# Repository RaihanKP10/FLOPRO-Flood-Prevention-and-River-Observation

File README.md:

# FLOPRO : Flood Prevention and River Observation

Proyek ini adalah Sistem Pemantauan Ketinggian Air Sungai yang menggunakan teknologi IoT untuk memberikan peringatan banjir secara real-time dengan mengukur ketinggian air sungai. Sistem ini dirancang untuk membantu manajemen bencana banjir dengan memberikan notifikasi kepada pemerintah daerah dan masyarakat tentang peningkatan ketinggian air, sehingga tindakan pencegahan dapat dilakukan sebelum banjir terjadi.

IoT dan Jaringan Sensor - [PROGRAM STUDI TEKNIK ELEKTRONIKA](https://elektronika.pens.ac.id/) - [POLITEKNIK ELEKTRONIKA NEGERI SURABAYA](https://www.pens.ac.id/)

`DOSEN PENGAMPU : Akhmad Hendriawan S.T.,M.T.`

`NIP. 197501272002121003`

## Daftar Isi
- [Fitur](https://github.com/RaihanKP10/FLOPRO-Flood-Prevention-and-River-Observation/blob/main/README.md#fitur)
- [Anggota Tim](https://github.com/RaihanKP10/FLOPRO-Flood-Prevention-and-River-Observation/blob/main/README.md#anggota-tim)
- [Demonstrasi Kalibrasi Sensor](https://github.com/RaihanKP10/FLOPRO-Flood-Prevention-and-River-Observation/blob/main/README.md#demonstrasi-kalibrasi-sensor)

## Fitur
- **Pemantauan Real-Time**: Mengukur ketinggian air sungai secara terus-menerus menggunakan sensor.
- **Transmisi Data**: Mengirimkan data ke server cloud melalui perangkat IoT.
- **Sistem Peringatan Banjir**: Memberikan peringatan ketika ketinggian air melebihi ambang batas.
- **Antarmuka Web dan Mobile**: Menampilkan data dan peringatan pada dasbor yang mudah digunakan.
- **Penyimpanan Data**: Menyimpan data untuk analisis dan prediksi.
- **Pengaturan Ambang Batas**: Menyesuaikan ambang batas sesuai tingkat risiko.

## Anggota Tim

| Foto                                                                                                          | NRP       | Nama                  | Jobdesk             | Akun                             |
|---------------------------------------------------------------------------------------------------------------|-----------|-----------------------|---------------------|----------------------------------|
|  | 2122600036 | Dafit Ody Endriantono | UI/UX Designer     | [Ody](https://github.com/DafitOdy-In) |
|  | 2122600037 | Thofail Syakirudin    | Hardware           | [Thofail](https://github.com/DzavanTS) |
|  | 2122600046 | Ahmad Miftahur Rif'at | Mechanical         | [Rif'at](https://github.com/AatForUX) |
|  | 2122600051 | Zanuar Dwi Novaliyanto | Mechanical         | [Zanuar](https://github.com/ZanuarDwiNovaliyanto) |
|  | 2122600056 | Moch Raihan Kemal P   | Software           | [Raihan](https://github.com/RaihanKP10) |
|  | 2122600060 | Asyraf Sulthan Zaky   | Project Manager    | [Asyraf](https://github.com/AsyrafSinclair) |

## Hardware Desain

Alat ini mengukur ketinggian air dengan sensor ultrasonik HCSR-04 dan mengirimkan data ke server untuk ditampilkan melalui aplikasi. Ketika ketinggian mendekati ambang batas, sistem memicu servo untuk membuka pintu air di bendungan. Karena alat berada di luar ruangan, data dikirim melalui modem WiFi, dan energi diperoleh dari panel surya mini yang disimpan dalam baterai.

---

---
## PPT FLOPRO

https://www.canva.com/design/DAGU0XxpfDs/OkEMPqyUYkoWt_qYXgOqGQ/edit?utm_content=DAGU0XxpfDs&utm_campaign=designshare&utm_medium=link2&utm_source=sharebutton

---

---

## Demonstrasi Kalibrasi Sensor
#### 1. Link Demonstrasi Kalibrasi Sensor HCSR04 :

https://github.com/user-attachments/assets/5eed2dfb-3297-49b0-9c64-bf10c1c43c4e
   
https://youtube.com/shorts/4SDvYGCIjRk?feature=share
   
Kalibrasi sensor HC-SR04 adalah proses penyesuaian sensor ultrasonik ini untuk meningkatkan akurasi dalam mengukur jarak. Sensor HC-SR04 bekerja dengan mengirimkan gelombang ultrasonik dari pemancar (transmitter) dan menghitung waktu yang dibutuhkan oleh gelombang tersebut untuk memantul kembali ke penerima (receiver) setelah mengenai suatu objek. Dengan menggunakan kecepatan suara sebagai acuan, sensor ini dapat menghitung jarak objek berdasarkan waktu tempuh gelombang.

#### 2. Link Demonstrasi Kalibrasi Servo MG90s :

https://github.com/user-attachments/assets/9af5d12e-d331-4dda-a720-6778b383e7d6
   
https://youtube.com/shorts/B2ZGl9izdCo?feature=share
   
Kalibrasi servo MG90S adalah proses penyetelan servo motor ini untuk memastikan bahwa sudut putarannya akurat sesuai dengan sinyal kontrol yang diterima. Servo MG90S adalah servo motor kecil yang banyak digunakan dalam proyek robotika dan sistem kontrol, dengan kemampuan untuk berputar pada sudut tertentu berdasarkan sinyal PWM (Pulse Width Modulation) yang diterimanya.

#### 3. Link Demonstrasi Kalibrasi Mini Speaker :

https://github.com/user-attachments/assets/9ce2ebc6-c74e-48cd-b972-0ce2e92cbb17
   
https://youtu.be/lZPbhcjN7L0
   
Kalibrasi mini speaker adalah proses penyesuaian output suara dari speaker kecil untuk mencapai kualitas audio yang optimal sesuai kebutuhan. Mini speaker sering digunakan dalam perangkat elektronik portabel dan sistem suara kecil. Kalibrasi pada mini speaker bertujuan untuk memastikan bahwa suara yang dihasilkan sesuai dengan frekuensi yang diinginkan, volume yang tepat, serta tanpa distorsi.

#### 4. Link Demonstrasi Koneksi OTA :

https://github.com/user-attachments/assets/de8e1125-ee2f-4111-9aa6-75a2dc0249be

https://youtu.be/pMJeovFwK_Y?si=bnQbwsUD5YesixBR

Demonstrasi Koneksi OTA (Over-the-Air): Pada bagian pertama, kita akan melihat langkah-langkah dalam mengatur koneksi OTA. Ini memungkinkan perangkat untuk menerima pembaruan firmware secara nirkabel, memudahkan Anda mengelola pembaruan sistem tanpa perlu koneksi fisik ke perangkat.

#### 5. Link Demonstrasi Pembuatan Firmware :

https://github.com/user-attachments/assets/bfa29fa6-aab0-4fcf-a872-c59f6ed02e61

https://youtu.be/gWfn4EX8Wdg?si=ucNGiH2ZgVsit7tk

Demonstrasi Pembuatan Firmware: Berikutnya, kita akan mendalami proses pembuatan firmware yang sesuai dengan perangkat IoT Anda. Di sini, kita akan membahas cara menyusun kode, mengompilasi, hingga mengunggah firmware yang telah dibuat.

#### 6. Link Demonstrasi Sistem Monitoring Baterai :

https://github.com/user-attachments/assets/31b2b31e-45c3-4f26-8fa8-c767af66bc61

https://youtu.be/-h_9dVcLRwE?si=lmYOK9LiICJJzn_O

Demonstrasi Sistem Monitoring Baterai: Terakhir, kita akan mengimplementasikan sistem monitoring baterai untuk memantau status baterai perangkat. Monitoring ini sangat penting agar kita dapat memprediksi daya tahan perangkat dan memastikan bahwa perangkat selalu aktif sesuai kebutuhan.

#### 7. Link Demonstrasi Wifi Manager:

https://github.com/user-attachments/assets/3f8c9bdd-fb43-4b81-9738-53641b77a450

https://youtu.be/Md__u2JPdc4?si=srvmaIoYwEQb-n4l

Konfigurasi Wifi Manager FLOPRO untuk Proyek IoT dan Jaringan Sensor: Bagian pertama tutorial ini akan mengulas proses konfigurasi Wifi Manager untuk perangkat FLOPRO. Langkah ini penting agar perangkat dapat terhubung dengan jaringan WiFi yang ada secara fleksibel dan otomatis, memungkinkan koneksi yang efisien di berbagai lokasi.

#### 8. Link Demonstrasi Simulasi FLOPRO Pada Bak Mandi (Mengilustrasikan Sungai) :

https://github.com/user-attachments/assets/f5d06698-10ce-430e-9a92-0ce6799bd68e

https://youtu.be/32SNqkH3HE4?si=-2HCcUrE732MUAwt

Simulasi Demo FLOPRO pada Bak Mandi (Mengilustrasikan Sungai): Di bagian kedua, kita akan melakukan simulasi dengan bak mandi sebagai representasi sungai untuk memperlihatkan bagaimana sistem FLOPRO bekerja dalam mengukur dan memantau kualitas air. Sistem ini menggunakan sensor untuk membaca data kualitas air secara real-time, yang nantinya dapat diakses dari jarak jauh.

#### 9. Link Demonstrasi Alat + Aplikasi FLOPRO :

https://github.com/user-attachments/assets/4c1feaa1-9933-437e-9100-74239c586628

https://youtu.be/wIVfHC5TFvU

Demonstrasi alat dan aplikasi FLOPRO menampilkan cara penggunaan dan fitur utama FLOPRO untuk mendukung aktivitas pengguna. Video ini menunjukkan langkah-langkah operasional alat, mulai dari instalasi hingga integrasi dengan aplikasi FLOPRO, yang memungkinkan kontrol dan pemantauan data secara real-time. Dengan demonstrasi ini, pengguna dapat memahami bagaimana FLOPRO bekerja secara praktis untuk meningkatkan efisiensi dan efektivitas alat FLOPRO

#### 10. Link Demonstrasi Aplikasi FLOPRO :

https://github.com/user-attachments/assets/227b0415-c697-41e6-8797-6734db90a10a

https://youtu.be/Y9suIjy_hSk

Demonstrasi aplikasi FLOPRO memperlihatkan fitur-fitur utama dan cara menggunakan aplikasi untuk memaksimalkan fungsinya. Video ini menjelaskan langkah-langkah cara daftar akun dan login akun, serta cara menggunakan aplikasi

---

---
## Tampilan Aplikasi FLOPRO
#### 1. Register :

Tampilan aplikasi FLOPRO bagian Register dirancang untuk memudahkan pengguna baru dalam membuat akun dan mengakses layanan aplikasi. Di halaman ini, pengguna akan diminta untuk mengisi informasi dasar seperti nama, email, dan kata sandi. Tampilan yang sederhana dan intuitif memastikan proses registrasi berjalan cepat dan mudah. Ada juga tombol Submit untuk menyelesaikan proses pendaftaran serta petunjuk tambahan yang membantu pengguna dalam mengisi data dengan benar.

### 2. Login :

Tampilan aplikasi FLOPRO bagian Login dirancang untuk memudahkan pengguna masuk ke akun mereka dengan cepat dan aman. Di halaman ini, terdapat kolom untuk memasukkan email dan kata sandi, dengan tombol Login untuk melanjutkan ke halaman utama aplikasi. Tampilan yang sederhana dan bersih membantu pengguna fokus saat mengisi informasi. Ada juga opsi Forgot Password bagi pengguna yang lupa kata sandi, serta pilihan untuk mendaftar bagi pengguna baru yang belum memiliki akun.

### 3. Dashboard :

Tampilan aplikasi FLOPRO pada bagian Dashboard memberikan akses cepat dan ringkas ke informasi utama serta fitur-fitur penting. Di halaman ini, pengguna dapat melihat ringkasan data secara real-time, status perangkat yang terhubung, serta grafik atau statistik yang relevan dengan aktivitas mereka. Dashboard dirancang dengan antarmuka yang intuitif dan visual yang menarik, sehingga memudahkan pengguna dalam memantau, mengontrol, dan mengakses fitur aplikasi lainnya. Navigasi yang sederhana memungkinkan pengguna untuk berpindah ke menu lain dengan mudah dan efisien.

### 4. Demo Aplikasi FLOPRO Pembacaan Data Sensor :
https://github.com/user-attachments/assets/2c82f72f-5ee5-42d2-a93c-78d115699a81

### 5. Demo Aplikasi FLOPRO Register & Login Akun :
https://github.com/user-attachments/assets/8cda75ff-3960-4abb-a7de-a9cabbc41a08

---

---
## Video Presentasi & Iklan FLOPRO
#### 1. Presentasi :
https://youtu.be/c4BK9ON1-bA?si=03641uwP3lWksoRz

Video ini menampilkan presentasi lengkap dari proyek IoT dan Jaringan Sensor dengan nama FLOPRO yang dikerjakan oleh tim mahasiswa D4 Teknik ELektronika B. Presentasi mencakup beberapa segmen utama:

Latar Belakang Proyek
Penjelasan awal tentang motivasi dan tujuan pembuatan alat ini. Proyek ini dirancang untuk mengatasi masalah tertentu dengan memanfaatkan teknologi IoT dan jaringan sensor.

Demo Hardware dan Aplikasi

Langkah-langkah instalasi dan penggunaan perangkat keras.
Tampilan langsung dari sensor yang digunakan dan bagaimana data dikumpulkan.
Demonstrasi aplikasi yang dikembangkan untuk memonitor data dari sensor secara real-time melalui platform IoT.
Penjelasan Isi GitHub

Struktur repositori GitHub yang menyimpan seluruh kode sumber dan dokumentasi proyek.
Penjelasan tentang file utama, cara kerja program, dan instruksi penggunaan yang tersedia di GitHub.

#### 2. Iklan :
https://youtube.com/shorts/QswNNAhAtY0?si=gQIX3H-hSb-66b26

Video ini menampilkan iklan produk dari proyek IoT dan Jaringan Sensor dengan nama FLOPRO_yang dikerjakan oleh tim mahasiswa D4 Teknik Elektronika B

&copy; 2024 FLOPRO. All rights reserved.

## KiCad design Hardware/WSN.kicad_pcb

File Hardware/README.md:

## Blok Diagram

Alat ini mengukur ketinggian air dengan sensor ultrasonik HCSR-04 dan mengirimkan data ke server untuk ditampilkan melalui aplikasi. Ketika ketinggian mendekati ambang batas, sistem memicu servo untuk membuka pintu air di bendungan. Karena alat berada di luar ruangan, data dikirim melalui modem WiFi, dan energi diperoleh dari panel surya mini yang disimpan dalam baterai.

---

## Hardware Desain

---

## Hardware Desain 3D

---

## Hardware

---

## Pengetesan Hardware Pada Wokwi

Pengetesan hardware dapat dilakukan pada simulasi online di Wokwi.
[Tes Hardware](https://wokwi.com/projects/411479674030035969)

---

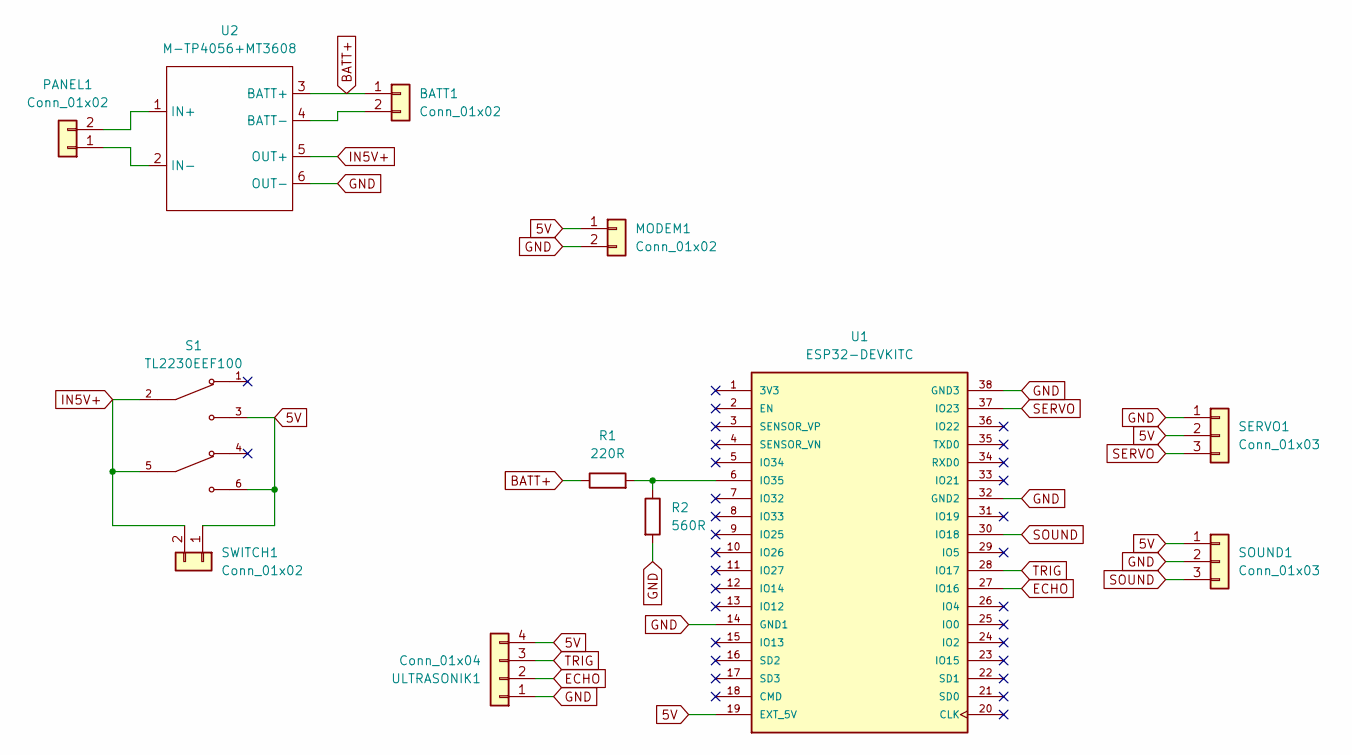
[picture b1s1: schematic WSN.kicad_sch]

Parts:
BATT1: Conn_01x02; PinHeader_1x02_P2.54mm_Vertical
MODEM1: Conn_01x02; PinHeader_1x02_P2.54mm_Vertical
PANEL1: Conn_01x02; PinHeader_1x02_P2.54mm_Vertical
R1: 220R; R_Axial_DIN0207_L6.3mm_D2.5mm_P10.16mm_Horizontal
R2: 560R; R_Axial_DIN0207_L6.3mm_D2.5mm_P10.16mm_Horizontal
S1: TL2230EEF100; SW_TL2230OAF140; PARTREV E
SERVO1: Conn_01x03; PinHeader_1x03_P2.54mm_Vertical
SOUND1: Conn_01x03; PinHeader_1x03_P2.54mm_Vertical
SWITCH1: Conn_01x02; PinHeader_1x02_P2.54mm_Vertical
U1: ESP32-DEVKITC; MODULE_ESP32-DEVKITC; PARTREV N/A
U2: M-TP4056+MT3608
ULTRASONIK1: Conn_01x04; PinHeader_1x04_P2.54mm_Vertical

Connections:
5V: MODEM1.1, S1.3, S1.6, SERVO1.2, SOUND1.1, SWITCH1.1, U1.19 (EXT_5V), ULTRASONIK1.4
BATT+: BATT1.1, R1.1, U2.3 (BATT+)
ECHO: U1.27 (IO16), ULTRASONIK1.2
GND: MODEM1.2, R2.2, SERVO1.1, SOUND1.2, U1.14 (GND1), U1.32 (GND2), U1.38 (GND3), U2.6 (OUT-), ULTRASONIK1.1
IN5V+: S1.2, S1.5, SWITCH1.2, U2.5 (OUT+)
unnamed: BATT1.2, U2.4 (BATT-)
unnamed: PANEL1.1, U2.2 (IN-)
unnamed: PANEL1.2, U2.1 (IN+)
unnamed: R1.2, R2.1, U1.6 (IO35)
SERVO: SERVO1.3, U1.37 (IO23)
SOUND: SOUND1.3, U1.30 (IO18)
TRIG: U1.28 (IO17), ULTRASONIK1.3

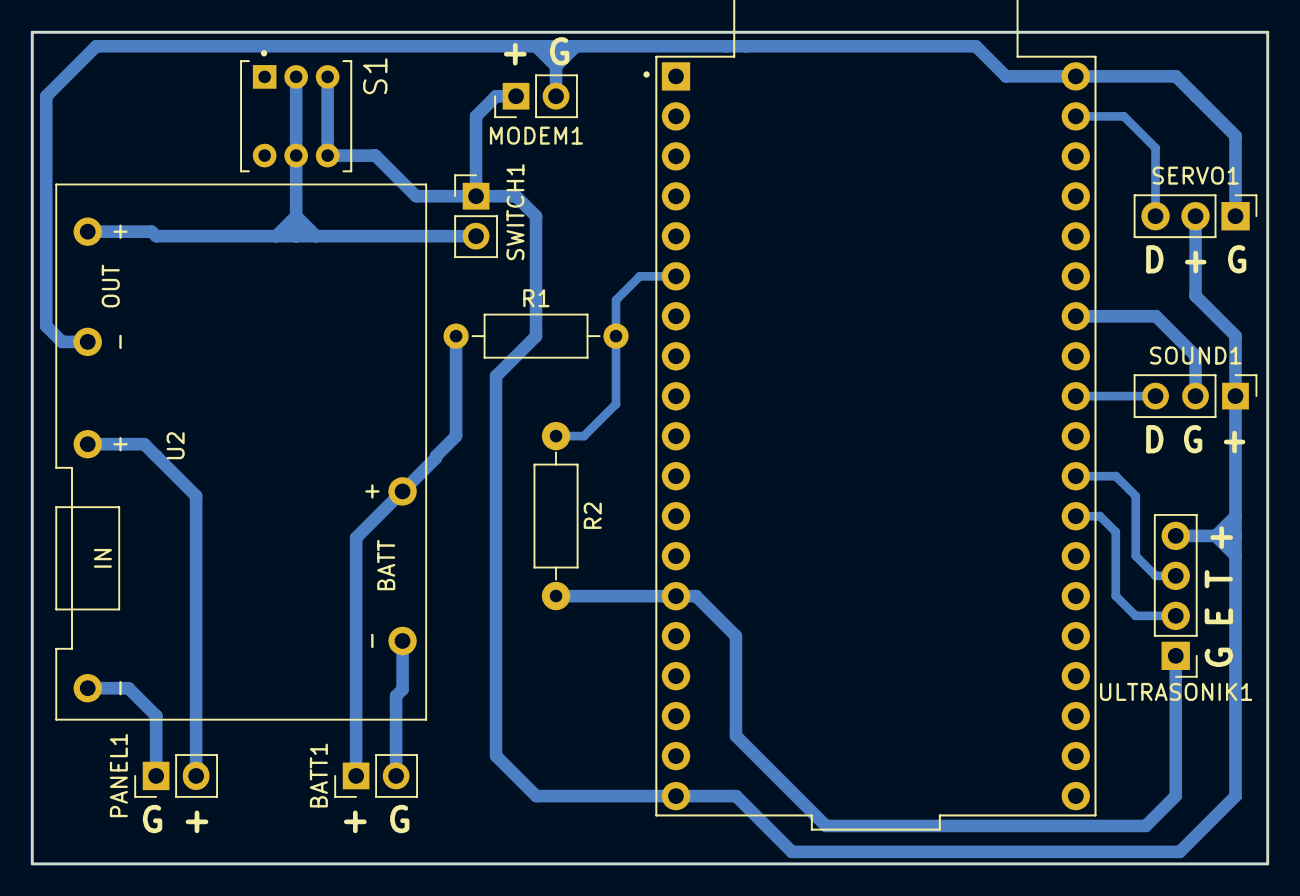
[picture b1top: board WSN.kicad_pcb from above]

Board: 2 copper layers, 78.5 x 52.8 mm, 12 parts (0 on the bottom side), 12 nets.

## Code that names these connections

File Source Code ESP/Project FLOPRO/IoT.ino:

#include <ESP32_Servo.h>
#include <WiFi.h>
#include <WiFiClient.h>
#include <WebServer.h>
#include <ElegantOTA.h>
#include <WiFiManager.h>
#include <MQTT.h>

#define Echo 16
#define Trigger 17
#define pServo 23
#define Sound 18
#define Batt 35
#define SetWifi 22

char ssid[32], pass[64];
const char* mqtt_server = "broker.hivemq.com";
const char* client_id = "Flopro IOT";

WiFiClient net;
MQTTClient client;
WebServer server(80);
Servo servo;

float Durasi, Jarak, rBatt, vBatt;
int jMin= 10, jMid= 20, jMax= 350;
int timeout = 120;
bool sBlink;
unsigned long mSonik, mSerial, mSound, mBlink;

void BacaSensor(){
  digitalWrite(Trigger, LOW);
  delayMicroseconds(2);
  digitalWrite(Trigger, HIGH);
  delayMicroseconds(10);
  digitalWrite(Trigger, LOW);
  Durasi = pulseIn(Echo, HIGH);
  Jarak = Durasi * 0.034 / 2;
  if(Jarak > jMax) Jarak= jMax;
}

void getSSIDPASW(){
  WiFiManager wm;
  String sssid = wm.getWiFiSSID(true);
  String spass = wm.getWiFiPass(true);
  sssid.toCharArray(ssid, sizeof(ssid));
  spass.toCharArray(pass, sizeof(pass));
}

void configurasiWIFI(){
  if(digitalRead(SetWifi) == LOW){
    digitalWrite(2, HIGH);
    WiFiManager wm;
    wm.resetSettings();
    wm.setConfigPortalTimeout(timeout);
    if (!wm.startConfigPortal("FLOPRO")) {
      Serial.println("failed to connect and hit timeout");
      delay(3000);
      ESP.restart();
    }
    getSSIDPASW();
    Serial.printf("\nWiFi connected to : ");
    Serial.println(ssid);
  }
}

void setup() {
  Serial.begin(9600);
  pinMode(Trigger, OUTPUT);
  pinMode(Echo, INPUT);
  pinMode(Sound, OUTPUT);
  pinMode(Batt, INPUT);
  pinMode(SetWifi, INPUT_PULLUP);
  pinMode(2, OUTPUT);
  digitalWrite(2, LOW);
  digitalWrite(Sound, LOW);
  servo.attach(pServo);
  servo.write(0);

  WiFi.mode(WIFI_STA);
  getSSIDPASW();
  Serial.printf("\nConnecting to : ");
  Serial.println(ssid);
  WiFi.begin(ssid, pass);
  while (WiFi.status() != WL_CONNECTED){
    delay(500);
    Serial.print(".");
    configurasiWIFI();
  }
  Serial.printf("\nWiFi connected to : ");
  Serial.println(ssid);
  Serial.print("IP address: ");
  Serial.println(WiFi.localIP());

  client.begin(mqtt_server, net);
  server.on("/", []() {
    server.send(200, "text/plain", "Hi! This is ElegantOTA FLOPRO.");
  });
  ElegantOTA.begin(&server);
  server.begin();
}

void loop() {
  configurasiWIFI();
  client.loop();
  server.handleClient();
  ElegantOTA.loop();
  
  rBatt= (analogRead(Batt) + 88) * 3.33 / 4095;
  vBatt= rBatt * (560 + 220) / 560;
    
  if(millis() - mBlink >= 1000){
    mBlink = millis();
    sBlink= !sBlink;
    digitalWrite(2, sBlink);
  }
  if(millis() - mSonik >= 50){
    mSonik = millis();
    BacaSensor();
  }
  if(millis() - mSerial >= 1000){
    mSerial = millis();
    Serial.println("Jarak: " + String(Jarak) + " cm");
    Serial.println("Baterai: " + String(vBatt) + " V");
    client.publish("odypens/jarak", String(Jarak));
    client.publish("odypens/vbatt", String(vBatt));
  }
  if(Jarak < jMin){
    servo.write(180);
    digitalWrite(Sound, HIGH);
    digitalWrite(Sound, LOW);
    Serial.println("Alarm");
    client.publish("odypens/servo", "Pintu Air Terbuka");
  }
  else if(Jarak >= jMin && Jarak <= jMid){
    if(millis() - mSound >= 5000){
      mSound = millis();
      digitalWrite(Sound, HIGH);
      digitalWrite(Sound, LOW);
      client.publish("odypens/sound", "Alarm Berbunyi");
    }
  }
  else{
    servo.write(0);
    digitalWrite(Sound, LOW);
    client.publish("odypens/servo", "Pintu Air Tertutup");
  }
}

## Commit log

2024-10-07 README.md
2024-10-10 Create ody
2024-10-12 Create Deskripsi
2024-10-12 Create test
2024-10-12 Create a
2024-10-12 Create test hardware
2024-10-12 Blok Diagram
    Blok Diagram
2024-10-12 Simulasi Hardware WokWI
    Simulasi Hardware
2024-10-12 Simulasi Hardware pada Wokwi
2024-10-12 Rename README.md
2024-10-12 Desain PCB
2024-10-12 DeleteSkematik.pdf
2024-10-12 Desain Hardware
2024-10-14 Create Design UI FLOPRO
2024-10-14 Create Sketch UI FLOPRO
2024-10-15 Create Design 3D
2024-10-19 Membuat folder form Checklist
2024-10-19 Create Desain dan Perencanaan
2024-10-19 Create Analisis dan Brainstorming
2024-10-19 Create cek
2024-10-19 buat folder
2024-10-20 Rename Design 3D to Desain 3D/Design 3D
2024-10-20 Create Source Code ESP
2024-10-20 Rename logo watersafe.jpg to Assets/logo watersafe.jpg
2024-10-20 Create ....
2024-10-20 Rename TheIdea.png to Mind Map Idea Of The Project
2024-10-20 Create Design UI UX
2024-10-21 Update Skematik
2024-10-21 Test
2024-10-21 Update Layout
2024-10-21 Create ...
2024-10-21 Update Desain PCB
2024-10-21 Sketsa
2024-10-21 Update desain PCB 3D
2024-10-21 Create Penginstallan Aplikasi & Flutter
2024-10-21 Penginstallan Aplikasi & Flutter
2024-10-24 Coba
2024-10-31 Update README.md dg markdown
2024-10-31 Update README.md dgn markdown
2024-11-10 Update Skematik dan Layout
2024-11-10 Upload PNG Skematik dan Layout
2024-11-10 Add Desain Kicad
2024-11-10 Update Desain Kicad
2024-11-10 Buat Folder Library
2024-11-10 Buat Folder OTA
2024-11-10 Buat Folder WiFi Manager
2024-11-10 Buat Folder Program FLOPRO
2024-11-10 Buat Folder Test Hardware
2024-11-10 Upload Program OTA
2024-11-10 Upload Program WiFi Manager
2024-11-10 Upload Program Test Hardware
2024-11-10 Upload Library ESP dan MQTT
2024-11-10 Upload Program Project FLOPRO
2024-11-10 Buat Folder MQTT
2024-11-10 Upload Program MQTT
2024-11-10 Upload Library WiFi Manager dan OTA
2024-11-10 Update Readme Video Hasil Program
2024-11-10 Upload Gambar Hardware Jadi
2024-11-10 Update Readme Gambar Hardware Jadi
2026-03-21 Fix formatting of lecturer's name in README.md
